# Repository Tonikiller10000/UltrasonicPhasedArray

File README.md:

# UltrasonicPhasedArray
An ultrasonic Phased Array made out of 8x 10mm ultrasonc transmitters.

## How it works:
The ultrasonic emitors generate 40KHz sinus sound waves whose phase can be controlled with the TC78H621FNG wave generator. 
By combining such type of waves, you can make interferences to increase or decrease the intensity of a wave.
If the waves have the same phase, the intensity of the wave doubles, and if the waves have oposite phases, they cancel out. 
This examples can be seen in the following picture:

<table>
  <tr>
    <td></td>
    <td>By combining multiple emitors, you can make a narrower sound wave like an sound LASER and also, by changing the phase of the waves, you can dirrect the waves at different points without any moving parts.</td>
  </tr>
</table>

This is the way that ecographyes and 5G work. 
Also, if you want to find more about this subjects like doppler effect, analog phased array and waves in general, you can read more at the following links:
- [Bitluni Phased arrays video + implementation](https://www.youtube.com/watch?v=z4uxC7ISd-c&t=649s)
- [Bitluni Phased arrays video 2](https://www.youtube.com/watch?v=Evao3XUUAOY)
- [wikiwand](https://www.wikiwand.com/en/Phased_array)
- [Wikipedia/ Phased Arrays](https://en.wikipedia.org/wiki/Phased_array)
- [Wikipedia/ Beam forming](https://en.wikipedia.org/wiki/Beamforming)
- [MathLab Phased Arrays playlist](https://www.youtube.com/playlist?list=PLn8PRpmsu08q9U0y7_63Dfz5cawEnicxi)
- [diy beamformer](https://www.youtube.com/watch?v=2QXKuEYR4Bw)
- [Beam forming](https://www.youtube.com/watch?v=HKpQP8H4JRc&t=1125s)
- [Phased arrays lecture](https://www.youtube.com/watch?v=LYyGkKP4Obg)
- [Hackaday phased arrays talk](https://www.youtube.com/watch?v=ytBmoL2wZLw&t=1472s)
- [Phased arryas paper](https://www.mdpi.com/2076-3417/8/9/1544)
- [Phased array signal processing](https://hackaday.io/page/13711-phased-array-signal-processing)

## Datasheets:
- schematic: https://github.com/Tonikiller10000/UltrasonicPhasedArray/blob/main/UltrasonicPhasedArray_Pictures/sch.png
- TC78H621FNG(Wave Generator): https://pdf1.alldatasheet.com/datasheet-pdf/view/1465439/TOSHIBA/TC78H621FNG.html
- TCT40-10TR1(Ultrasonic transmitter): https://www.mantech.co.za/datasheets/products/tct40-10tr1.pdf

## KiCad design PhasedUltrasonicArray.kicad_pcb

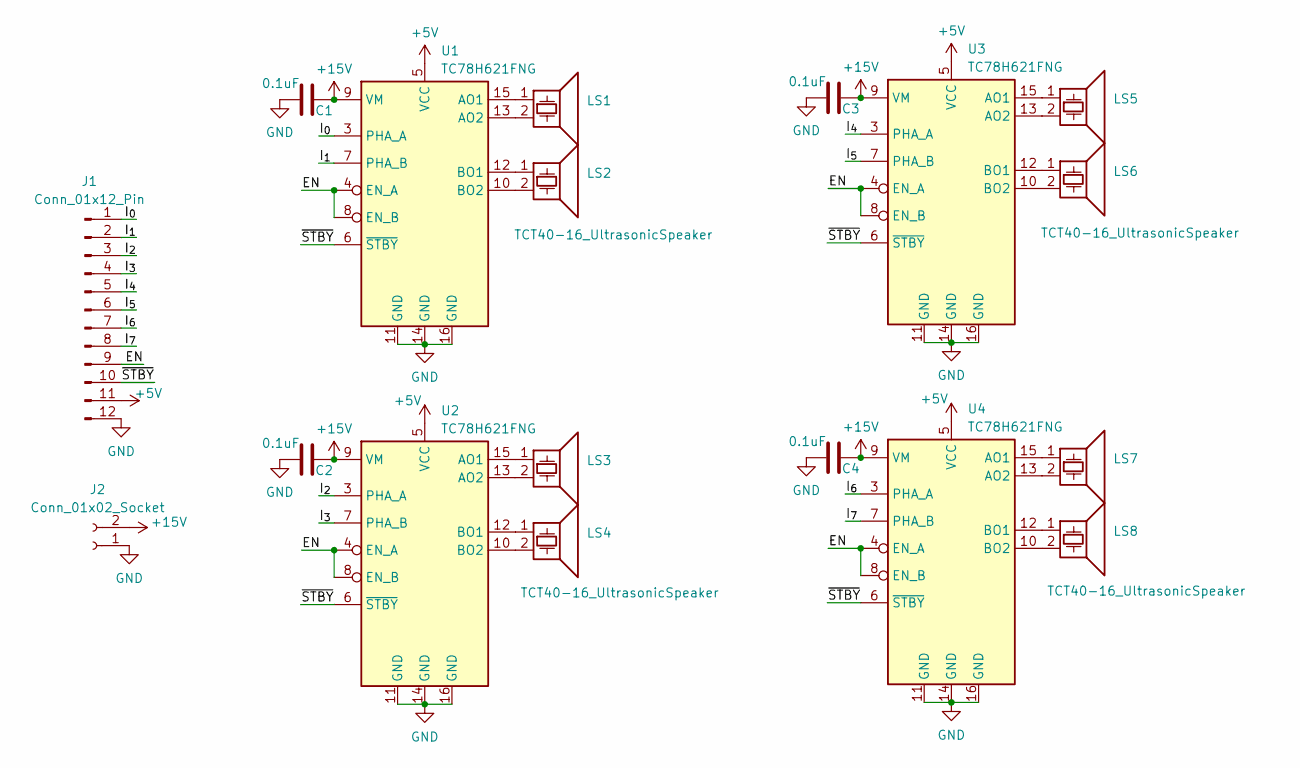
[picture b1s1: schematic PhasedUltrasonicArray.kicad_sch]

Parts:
C1, C2, C3, C4: 0.1uF
J1: Conn_01x12_Pin
J2: Conn_01x02_Socket
LS1, LS2, LS3, LS4, LS5, LS6, LS7, LS8: TCT40-16_UltrasonicSpeaker
U1, U2, U3, U4: TC78H621FNG

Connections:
+5V: J1.11, U1.5 (VCC), U2.5 (VCC), U3.5 (VCC), U4.5 (VCC)
+15V: C1.2, C2.2, C3.2, C4.2, J2.2, U1.9 (VM), U2.9 (VM), U3.9 (VM), U4.9 (VM)
/EN: J1.9, U1.4 (EN_A), U1.8 (EN_B), U2.4 (EN_A), U2.8 (EN_B), U3.4 (EN_A), U3.8 (EN_B), U4.4 (EN_A), U4.8 (EN_B)
/I_{0}: J1.1, U1.3 (PHA_A)
/I_{1}: J1.2, U1.7 (PHA_B)
/I_{2}: J1.3, U2.3 (PHA_A)
/I_{3}: J1.4, U2.7 (PHA_B)
/I_{4}: J1.5, U3.3 (PHA_A)
/I_{5}: J1.6, U3.7 (PHA_B)
/I_{6}: J1.7, U4.3 (PHA_A)
/I_{7}: J1.8, U4.7 (PHA_B)
/~STBY: J1.10, U1.6 (~STBY), U2.6 (~STBY), U3.6 (~STBY), U4.6 (~STBY)
GND: C1.1, C2.1, C3.1, C4.1, J1.12, J2.1, U1.11 (GND), U1.14 (GND), U1.16 (GND), U2.11 (GND), U2.14 (GND), U2.16 (GND), U3.11 (GND), U3.14 (GND), U3.16 (GND), U4.11 (GND), U4.14 (GND), U4.16 (GND)
unnamed: LS1.1, U1.15 (AO1)
unnamed: LS1.2, U1.13 (AO2)
unnamed: LS2.1, U1.12 (BO1)
unnamed: LS2.2, U1.10 (BO2)
unnamed: LS3.1, U2.15 (AO1)
unnamed: LS3.2, U2.13 (AO2)
unnamed: LS4.1, U2.12 (BO1)
unnamed: LS4.2, U2.10 (BO2)
unnamed: LS5.1, U3.15 (AO1)
unnamed: LS5.2, U3.13 (AO2)
unnamed: LS6.1, U3.12 (BO1)
unnamed: LS6.2, U3.10 (BO2)
unnamed: LS7.1, U4.15 (AO1)
unnamed: LS7.2, U4.13 (AO2)
unnamed: LS8.1, U4.12 (BO1)
unnamed: LS8.2, U4.10 (BO2)

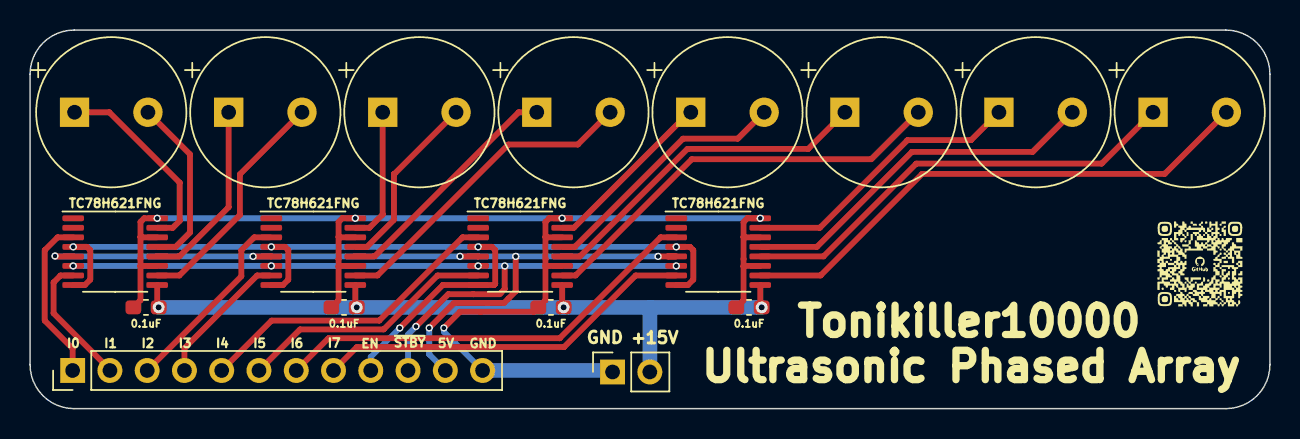
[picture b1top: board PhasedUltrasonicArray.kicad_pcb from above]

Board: 2 copper layers, 84.5 x 25.8 mm, 18 parts (0 on the bottom side), 29 nets.

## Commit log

2024-01-13 init
2024-02-26 info
